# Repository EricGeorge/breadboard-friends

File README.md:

breadboard-friends
==================

A collection of cute breakout boards riding solderless breadboards, mostly for analog audio works

These PCB layouts and schematics are released under a Creative Commons cc-by-sa
3.0 license.

NOTE:  This repo has been forked from Mutable Instruments breadboard-friends and adds
1 new board - a MIDI IN/OUT breakout board.  It uses a similar design to the MIDI circuit in
Mutable Instrument Shruthi schematics.  It requires +5V power on VCC.  VEE is not 
connected.

BBF-MIDI Bill of Materials (BOM)

| Reference | Value | Part |
| ------------- | ------------- | ------------ |
| C1 | 0.1uF | 5mm ceramic cap |
| D1 | 1N4148 | Diode |
| J1 | MIDI IN | SDS-50J |
| J2 | MIDI OUT | SDS-50J |
| J3 | To Rx/From Tx | 2 pin male header |
| J4, J5 | Power headers | 10 pin DIL male header |
| R1, R2 | 220 Ω | 1% metal film resistor |
| R3 | 10k Ω | 1% metal film resistor |
| U1 | 6N137 | optical coupler 8-dip |

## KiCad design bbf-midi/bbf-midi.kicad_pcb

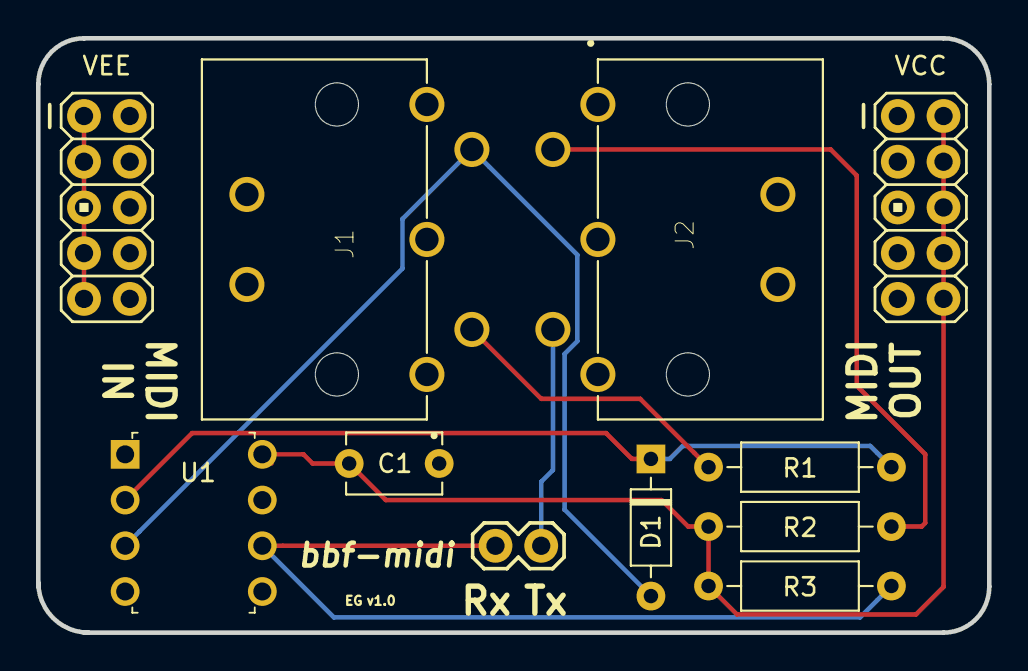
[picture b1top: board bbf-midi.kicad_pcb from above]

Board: 2 copper layers, 52.8 x 33.0 mm, 11 parts (0 on the bottom side), 9 nets.

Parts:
C1: 0.1uF; C_Disc_D5.1mm_W3.2mm_P5.00mm
D1: 1N4148; D_DO-35_SOD27_P7.62mm_Horizontal
J1: MIDI IN; CUI_SDS-50J
J2: MIDI OUT; CUI_SDS-50J
J3: To Rx/From Tx; 1X02
J4, J5: Power; AVR_ICSP
R1, R2: 220; R_Axial_DIN0207_L6.3mm_D2.5mm_P10.16mm_Horizontal
R3: 10k; R_Axial_DIN0207_L6.3mm_D2.5mm_P10.16mm_Horizontal
U1: 6N137; DIP-8_W7.62mm

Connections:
GND: C1.2, J2.2, J4.1, J4.3, J4.5, J4.7, J4.9, J5.2, J5.4, J5.6, J5.8, J5.10, U1.5
unnamed: D1.1, R1.1, U1.2
unnamed: D1.2, J1.5, U1.3
unnamed: J1.4, R1.2
unnamed: J2.4, R2.2
Rx: J3.1, R3.2, U1.6
Tx: J2.5, J3.2
VCC: C1.1, J4.2, J4.4, J4.6, J4.8, J4.10, R2.1, R3.1, U1.8
VEE: J5.1, J5.3, J5.5, J5.7, J5.9

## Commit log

2019-03-11 bbf-midi first commit

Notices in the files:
bbf-midi/bbf-midi.kicad_pcb:
License:  CC BY 4.0
